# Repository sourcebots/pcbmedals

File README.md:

# pcbmedals
This repsitory contains the schematic, board files and firmware files for the PCB medals.

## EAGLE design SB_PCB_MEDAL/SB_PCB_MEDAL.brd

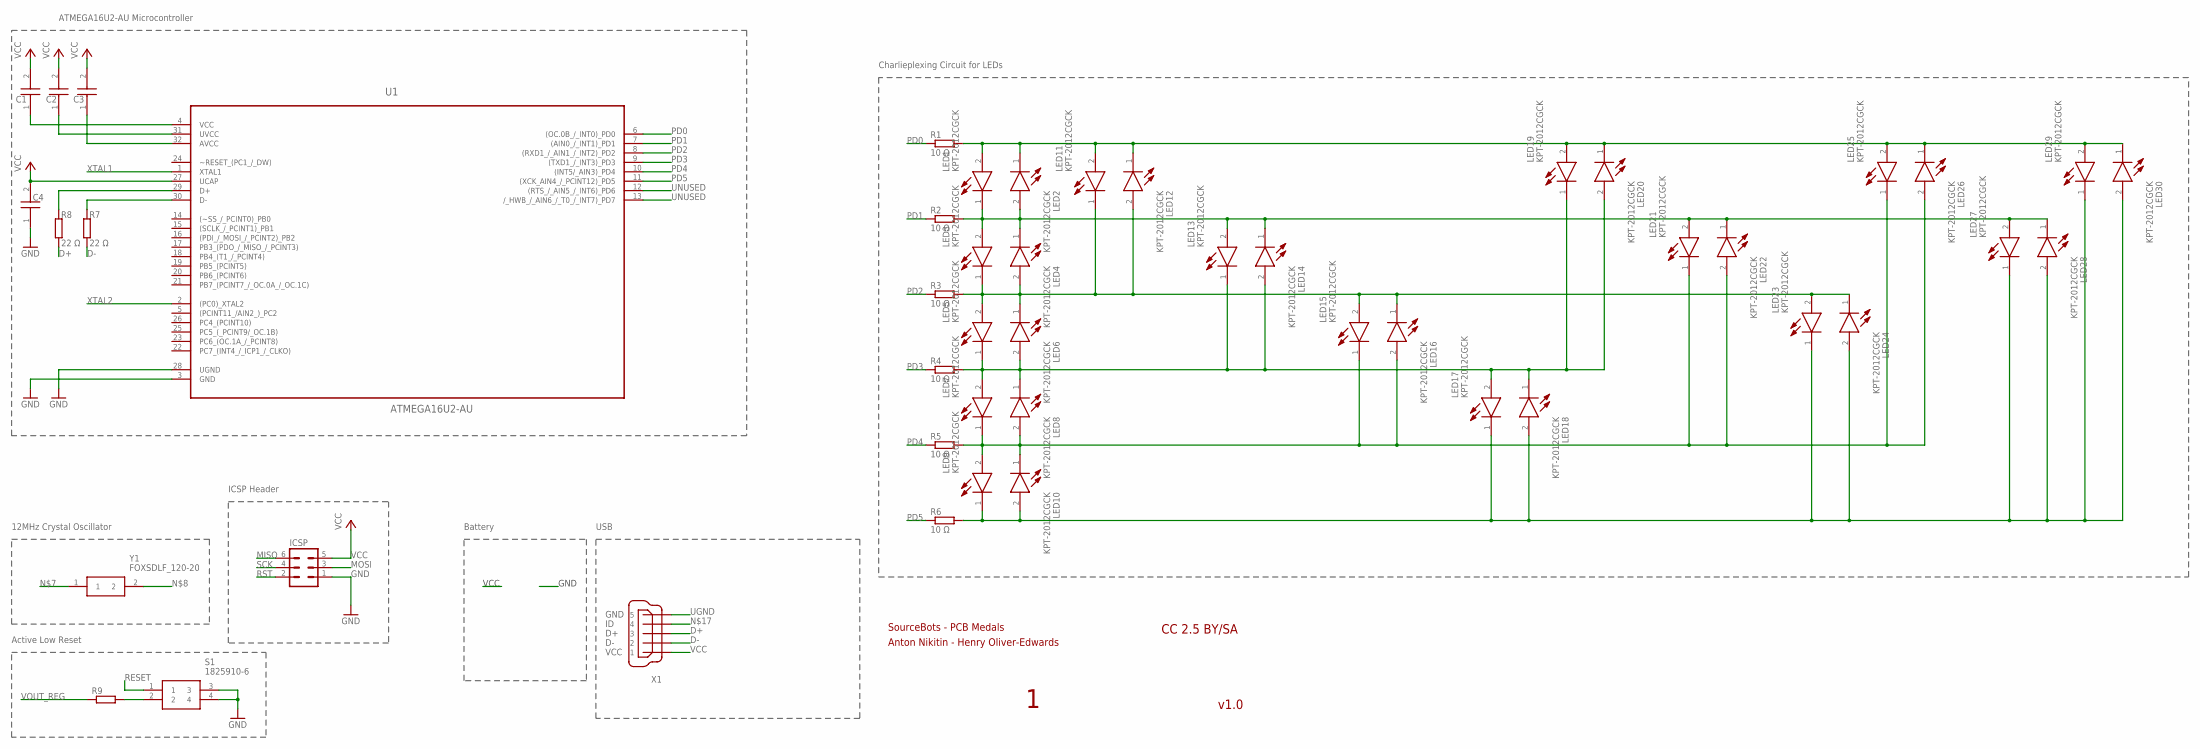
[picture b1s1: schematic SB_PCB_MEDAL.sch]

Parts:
C1, C2, C3, C4: MC0805B104K250CT; CAPC2012X60N
ICSP: MA03-2
LED1, LED2, LED3, LED4, LED5, LED6, LED7, LED8, LED9, LED10, LED11, LED12, LED13, LED14, LED15, LED16, LED17, LED18, LED19, LED20, LED21, LED22, LED23, LED24, LED25, LED26, LED27, LED28, LED29, LED30: KPT-2012CGCK; LEDC2012X78N
R1, R2, R3, R4, R5, R6: 10 Ω; M0805
R7, R8: 22 Ω; M0805
R9: R-EU_0204/7; 0204/7
S1: 1825910-6
U1: ATMEGA16U2-AU; QFP80P900X900X120-32N
X1: MINI-USB_SHIELD5P2-32005-601; 32005-601
Y1: FOXSDLF_120-20; FOXSDLF/120-20

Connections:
D+: R8.1, X1.3
D-: R7.1, X1.2
GND: C4.1, ICSP.1, S1.3, S1.4, U1.3 (GND)
MISO: ICSP.6
MOSI: ICSP.3
unnamed: LED1.2 (A), LED2.1 (K), LED11.2 (A), LED12.1 (K), LED19.2 (A), LED20.1 (K), LED25.2 (A), LED26.1 (K), LED29.2 (A), LED30.1 (K), R1.2
unnamed: LED1.1 (K), LED2.2 (A), LED3.2 (A), LED4.1 (K), LED13.2 (A), LED14.1 (K), LED21.2 (A), LED22.1 (K), LED27.2 (A), LED28.1 (K), R2.2
unnamed: LED3.1 (K), LED4.2 (A), LED5.2 (A), LED6.1 (K), LED11.1 (K), LED12.2 (A), LED15.2 (A), LED16.1 (K), LED23.2 (A), LED24.1 (K), R3.2
unnamed: LED5.1 (K), LED6.2 (A), LED7.2 (A), LED8.1 (K), LED13.1 (K), LED14.2 (A), LED17.2 (A), LED18.1 (K), LED19.1 (K), LED20.2 (A), R4.2
unnamed: LED7.1 (K), LED8.2 (A), LED9.2 (A), LED10.1 (K), LED15.1 (K), LED16.2 (A), LED21.1 (K), LED22.2 (A), LED25.1 (K), LED26.2 (A), R5.2
unnamed: LED9.1 (K), LED10.2 (A), LED17.1 (K), LED18.2 (A), LED23.1 (K), LED24.2 (A), LED27.1 (K), LED28.2 (A), LED29.1 (K), LED30.2 (A), R6.2
unnamed: C1.1, U1.4 (VCC)
unnamed: R9.2, S1.2
unnamed: C3.1, U1.32 (AVCC)
unnamed: R8.2, U1.29 (D+)
unnamed: R7.2, U1.30 (D-)
PD0: R1.1, U1.6 ((OC.0B_/_INT0)_PD0)
PD1: R2.1, U1.7 ((AIN0_/_INT1)_PD1)
PD2: R3.1, U1.8 ((RXD1_/_AIN1_/_INT2)_PD2)
PD3: R4.1, U1.9 ((TXD1_/_INT3)_PD3)
PD4: R5.1, U1.10 ((INT5/_AIN3)_PD4)
PD5: R6.1, U1.11 ((XCK_AIN4_/_PCINT12)_PD5)
RESET: S1.1
RST: ICSP.2
UGND: U1.28 (UGND), X1.5
USCK: ICSP.4
UVCC: C2.1, U1.31 (UVCC)
VCC: C1.2, C2.2, C3.2, C4.2, ICSP.5, U1.27 (UCAP), X1.1
VOUT_REG: R9.1
XTAL1: U1.1 (XTAL1)
XTAL2: U1.2 ((PC0)_XTAL2)

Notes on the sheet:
VCC
MOSI
GND
MISO
SCK
RST
Anton Nikitin - Henry Oliver-Edwards
SourceBots - PCB Medals
v1.0
CC 2.5 BY/SA
ATMEGA16U2-AU Microcontroller
Charlieplexing Circuit for LEDs
ICSP Header
Battery
USB
12MHz Crystal Oscillator
UNUSED
Active Low Reset

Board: 2 copper layers, 48 parts (8 on the bottom side), 23 nets, no tracks yet.

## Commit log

2017-11-28 added readme
2017-11-30 added button cell to schematic and vcc line
2017-11-30 modified connections to button cell and added text for the ICSP header to the PCB
2017-11-30 removed 24mm button cell from schematic and replaced with smaller 12mm due to size issues on the board
2017-12-01 added one LED to the schematic
2017-12-01 completed circuit for charliplexed LEDs
2017-12-02 removed 2 additional LEDs
2017-12-02 re-did some wiring
2017-12-02 added labels to chip and LED resistors
2017-12-02 added design rule files for OSHPark
2017-12-03 added labels to pins
2017-12-04 add design rules for oshpark
2017-12-04 removed additional files
2017-12-04 literally copy and paste files from other branch into the master because EAGLE files and branches hate each other as much as North Korea and the US....
2017-12-04 added surface mountable button
2017-12-04 added more labels to the board
2017-12-04 added schematic pdf
2018-03-14 modify board
2018-03-14 modify led position and add usb
2018-03-14 modify boards
